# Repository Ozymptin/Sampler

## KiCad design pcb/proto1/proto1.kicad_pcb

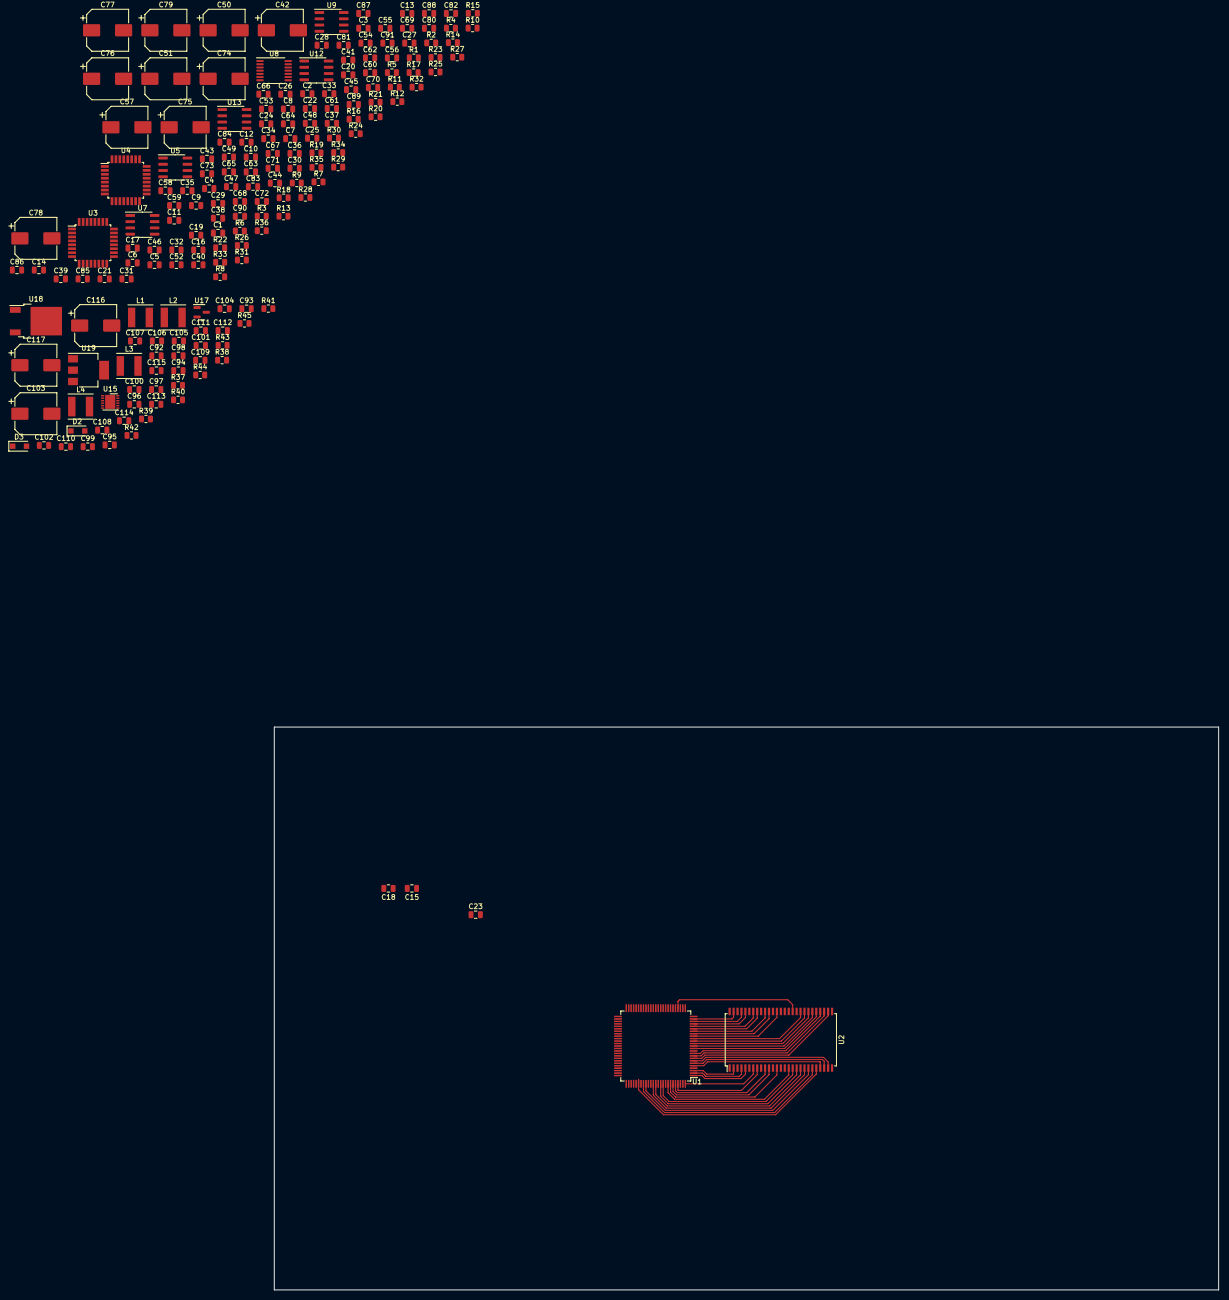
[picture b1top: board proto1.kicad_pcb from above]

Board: 4 copper layers, 191.8 x 114.3 mm, 182 parts (0 on the bottom side), 116 nets.

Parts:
C1, C2, C13, C14, C15, C21, C23, C27, C34, C37, C41, C44, C49, C56, C58, C59, C64, C65, C84, C85, C86, C87, C97, C100, C101, C113, C114, C115: 10uF; C_0805_2012Metric
C3, C4, C5, C6, C16, C17, C18, C19, C20, C22, C24, C25, C26, C28, C29, C30, C32, C33, C35, C36, C39, C40, C43, C46, C47, C48, C53, C54, C55, C60, C61, C66, C67, C88, C89, C90, C91, C92, C94, C98, C99, C102, C108, C109: 0.1uF; C_0805_2012Metric
C7, C8, C38, C45, C110, C111, C112: 1uF; C_0805_2012Metric
C9, C10, C11, C12: C; C_0805_2012Metric
C31, C52, C68, C69, C70, C71, C72, C73, C95, C96: 100pF; C_0805_2012Metric
C42, C50, C51, C57, C74, C75, C76, C77, C78, C79, C103, C116, C117: 220uF; CP_Elec_8x10
C62, C63: 14pF; C_0805_2012Metric
C80, C81, C82, C83: 27pF; C_0805_2012Metric
C93, C104, C105: 1nF; C_0805_2012Metric
C106, C107: 10nF; C_0805_2012Metric
D2, D3: ?; D_SOD-123F
L1, L2: 50uH; L_Taiyo-Yuden_NR-50xx
L3, L4: L; L_Taiyo-Yuden_NR-50xx
R1, R2, R3, R4, R5, R8, R9, R11, R29, R30, R31, R32, R33, R34, R35, R36, R41, R42: 10K; R_0805_2012Metric
R6, R12, R39, R40, R44, R45: 1K; R_0805_2012Metric
R7, R13: 68R; R_0805_2012Metric
R10, R14: 22K; R_0805_2012Metric
R15, R16, R17, R18, R19, R20: 100R; R_0805_2012Metric
R21, R22: 220K; R_0805_2012Metric
R23, R24, R25, R26, R27, R28: 100K; R_0805_2012Metric
R37: 124K; R_0805_2012Metric
R38: 113K; R_0805_2012Metric
R43: 500K; R_0805_2012Metric
U1: ATSAM4C4; LQFP-100_14x14mm_P0.5mm
U2: NDS36P; TSOP-II-54_22.2x10.16mm_P0.8mm
U3, U4: ATSAMD21E17D-A; TQFP-32_7x7mm_P0.8mm
U5, U7, U9, U12, U13: NE5532; SOIC-8_3.9x4.9mm_P1.27mm
U8: PCM1807; TSSOP-14_4.4x5mm_P0.65mm
U15: R1283K; DFN-12-1EP_3x3mm_P0.5mm_EP2.05x2.86mm
U17: ?; SOT-23
U18: ?; TO-252-2
U19: AP7361C-33E; SOT-223-3_TabPin2

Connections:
+1V2: C14.1, C17.1, C22.1, C26.1, C29.1, C36.1, U1.11 (VDDCORE), U1.44 (VDDCORE), U1.53 (VDDPLL), U1.63 (VDDCORE), U1.86 (VDDOUT), U1.89 (VDDCORE)
+3V3: C1.1, C2.1, C3.1, C4.1, C5.1, C6.1, C13.1, C15.1, C16.1, C18.1, C21.1, C23.1, C24.1, C25.1, C28.1, C35.1, C37.1, C39.1, C40.1, C41.1, C43.1, C45.1, C49.1, C53.1, C115.1, U1.33 (VDDIO), U1.34 (VDDBU), U1.49 (VDDIO), U1.76 (VDDIO), U1.85 (VDDIN), U1.92 (VDDLCD), U1.99 (VDDIO), U2.1 (VDD), U2.3 (VDDQ), U2.9 (VDDQ), U2.14 (VDD), U2.27 (VDD), U2.43 (VDDQ), U2.49 (VDDQ), U3.9 (VDDANA), U3.30 (VDDIN), U4.9 (VDDANA), U4.30 (VDDIN), U8.4 (VDD), U19.3 (VO)
+5V: C102.1, C103.1, C110.1, L1.1, U15.8 (Vcc), U15.11 (PVcc), U19.1 (VI)
+5VA: C27.1, C30.1, C34.1, C38.1, U8.3 (VCC)
+12V: C58.1, C60.1, C64.1, C66.1, C84.1, C86.1, C88.1, C90.1, C104.1, C106.1, C108.1, C111.1, C113.1, C116.1, U5.8 (V+), U7.8 (V+), U9.8 (V+), U12.8 (V+), U17.1 (VO)
-12V: C59.2, C61.1, C65.2, C67.1, C85.2, C87.2, C89.1, C91.1, C105.1, C107.1, C109.1, C112.1, C114.1, C117.2, U5.4 (V-), U7.4 (V-), U9.4 (V-), U12.4 (V-), U18.3 (VO)
/A0: U1.81 (PB13/AD3), U2.23 (A0)
/A1: U1.5 (PB19), U2.24 (A1)
/A2: U1.6 (PB8), U2.25 (A2)
/A3: U1.7 (PB22), U2.26 (A3)
/A4: U1.8 (PB30), U2.29 (A4)
/A5: U1.9 (PB25), U2.30 (A5)
/A6: U1.10 (PB24), U2.31 (A6)
/A7: U1.12 (PB29), U2.32 (A7)
/A8: U1.13 (PB9), U2.33 (A8)
/A9: U1.14 (PB10), U2.34 (A9)
/A10: U1.83 (PA4/AD1), U2.22 (A10)
/A11: U1.15 (PB11), U2.35 (A11)
/A12: U1.16 (PB12), U2.36 (A12)
/BA0: U1.87 (PB21), U2.20 (BA0)
/BA1: U1.84 (PA12/AD0), U2.21 (BA1)
/CAS: U1.91 (PB27), U2.17 (~CAS)
/CLK: U1.29 (PC9), U2.38 (CLK)
/CS: U1.88 (PB20), U2.19 (~CS)
/DQ0: U1.3 (PB18), U2.2 (DQ0)
/DQ1: U1.2 (PB7), U2.4 (DQ1)
/DQ2: U1.1 (PB6), U2.5 (DQ2)
/DQ3: U1.100 (PA2), U2.7 (DQ3)
/DQ4: U1.97 (PB17), U2.8 (DQ4)
/DQ5: U1.96 (PA1), U2.10 (DQ5)
/DQ6: U1.95 (PB16), U2.11 (DQ6)
/DQ7: U1.94 (PB28), U2.13 (DQ7)
/DQ8: U1.17 (PB14), U2.42 (DQ8)
/DQ9: U1.18 (PB15), U2.44 (DQ9)
/DQ10: U1.19 (PA26), U2.45 (DQ10)
/DQ11: U1.20 (PA25), U2.47 (DQ11)
/DQ12: U1.21 (PA24), U2.48 (DQ12)
/DQ13: U1.22 (PA20), U2.50 (DQ13)
/DQ14: U1.23 (PA19), U2.51 (DQ14)
/DQ15: U1.24 (PA18), U2.53 (DQ15)
/RAS: U1.90 (PA0), U2.18 (~RAS)
/WE: U1.93 (PB26), U2.16 (~WE)
ADC_CH_CS_0: U1.82 (PA5/AD2), U3.1 (PA00)
ADC_CH_MISO: U1.62 (PA6), U3.8 (PA07)
ADC_CH_MOSI: U1.98 (PA7), U3.7 (PA06)
ADC_CH_SCK: U1.25 (PA8), U3.6 (PA05)
ADC_I2S_FS: U3.14 (PA11), U8.7 (LRCK)
ADC_I2S_MCK: U3.12 (PA09), U8.6 (SCKI)
ADC_I2S_SCK: U3.13 (PA10), U8.8 (BCK)
ADC_I2S_SD: U3.11 (PA08), U8.9 (DOUT)
ADC_LIN: C50.1, U8.13 (VinL)
ADC_RIN: C51.1, U8.14 (VinR)
ADC_SPI_CS: U3.18 (PA17), U8.12 (MS)
ADC_SPI_MOSI: U3.20 (PA19), U8.10 (MD)
ADC_SPI_SCK: U3.19 (PA18), U8.11 (MC)
DAC_CH_CS_0: U1.58 (PC2), U4.1 (PA00)
DAC_CH_MISO: U1.57 (PC3), U4.8 (PA07)
DAC_CH_MOSI: U1.56 (PC4), U4.7 (PA06)
DAC_CH_SCK: U1.55 (PC5), U4.6 (PA05)
EN: R43.1, R45.1, U15.5 (CE)
GND: C1.2, C2.2, C3.2, C4.2, C5.2, C6.2, C7.2, C8.2, C9.1, C10.1, C11.1, C12.1, C13.2, C14.2, C15.2, C16.2, C17.2, C18.2, C19.2, C20.2, C21.2, C22.2, C23.2, C24.2, C25.2, C26.2, C27.2, C28.2, C29.2, C30.2, C32.2, C33.2, C35.2, C36.2, C37.2, C39.2, C40.2, C43.2, C44.2, C46.2, C47.2, C48.2, C49.2, C53.2, C54.2, C55.2, C56.2, C58.2, C59.1, C60.2, C61.2, C62.2, C63.2, C64.2, C65.1, C66.2, C67.2, C68.2, C69.2, C70.1, C71.2, C72.1, C73.2, C82.2, C83.2, C84.2, C85.1, C86.2, C87.1, C88.2, C89.2, C90.2, C91.2, C92.2, C93.2, C94.2, C97.2, C98.2, C99.2, C100.2, C101.2, C102.2, C103.2, C104.2, C105.2, C106.2, C107.2, C108.2, C109.2, C110.2, C111.2, C112.2, C113.2, C114.2, C115.2, C116.2, C117.1, L2.2, R10.2, R14.2, R21.2, R22.2, R23.1, R24.2, R25.1, R26.2, R27.2, R28.2, R33.2, R34.2, R41.1, R43.2, U1.4 (GND), U1.42 (GND), U1.52 (GND), U1.78 (GND), U2.6 (VSSQ), U2.12 (VSSQ), U2.28 (VSS), U2.41 (VSS), U2.46 (VSSQ), U2.52 (VSSQ), U2.54 (VSS), U3.10 (GND), U3.28 (GND), U4.10 (GND), U4.28 (GND), U5.5 (+), U7.3 (+), U8.2 (AGND), U8.5 (DGND), U15.10 (GND), U15.12 (PGND), U15.13 (PAD), U17.3 (GND), U18.1 (GND), U19.2 (GND)
LAUX_OUT: R1.2, U12.1, U12.2 (-)
LOUT: C80.2, R2.2, R35.2, U13.1
unnamed: C7.1, U3.29 (VDDCORE)
unnamed: C8.1, U4.29 (VDDCORE)
unnamed: C9.2, U3.15 (PA14)
unnamed: C10.2, U3.16 (PA15)
unnamed: C11.2, U4.15 (PA14)
unnamed: C12.2, U4.16 (PA15)
unnamed: C31.1, R7.2, U5.1
unnamed: C31.2, R5.2, R6.2, U5.3 (+)
unnamed: C34.2, C38.2, C41.2, C45.2
unnamed: C42.1, R5.1, R6.1, R7.1
unnamed: C42.2, R10.1
unnamed: C44.1, C48.1, U8.1 (VREF)
unnamed: C52.1, R13.2, U9.1
unnamed: C52.2, R11.2, R12.2, U9.3 (+)
unnamed: C57.1, R11.1, R12.1, R13.1
unnamed: C57.2, R14.1
unnamed: C68.1, C74.1, R15.1, R21.1
unnamed: C69.1, C75.1, R16.1, R22.1
unnamed: C70.2, C76.1, R17.1, R23.2
unnamed: C71.1, C77.1, R18.1, R24.1
unnamed: C72.2, C78.1, R19.1, R25.2
unnamed: C73.1, C79.1, R20.1, R26.1
unnamed: C74.2, R27.1, U12.3 (+)
unnamed: C75.2, R28.1, U7.5 (+)
unnamed: C76.2, R29.2
unnamed: C77.2, R30.2
unnamed: C78.2, R31.2
unnamed: C79.2, R32.2
unnamed: C80.1, R29.1, R35.1, U13.2 (-)
unnamed: C81.1, R31.1, R36.1, U9.6 (-)
unnamed: C82.1, R30.1, R33.1, U13.3 (+)
unnamed: C83.1, R32.1, R34.1, U9.5 (+)
unnamed: C92.1, R42.1, U15.7 (Vref)
unnamed: C95.1, R39.2
unnamed: C95.2, R37.2, R41.2, U15.9 (Vfb1)
unnamed: C96.1, R40.2
unnamed: C96.2, R38.2, R42.2, U15.6 (Vfb2)
unnamed: C98.1, C100.1, L3.2, U17.2 (VI)
unnamed: C99.1, C101.1, L4.2, U18.2 (VI)
unnamed: D2.1 (K), L3.1, R37.1, R39.1
unnamed: D2.2 (A), L1.2, U15.2 (Lx1)
unnamed: D3.1 (K), L2.1, U15.3 (Lx2)
unnamed: D3.2 (A), L4.1, R38.1, R40.1, U15.4 (Voutn)
unnamed: R1.1, R2.1, R8.2, U7.2 (-)
unnamed: R3.1, R4.1, R9.2, U5.6 (-)
unnamed: R8.1, U7.1
unnamed: R9.1, U5.7
RAUX_OUT: R3.2, U7.6 (-), U7.7
RESET: U1.48 (NRST), U4.26 (~RESET)
ROUT: C81.2, R4.2, R36.2, U9.7
VBUS: C93.1, C94.1, R44.1
XIN: C62.1, U1.50 (PA30/XIN)
XOUT: C63.1, U1.51 (PA31/XOUT)

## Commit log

2022-02-25 Push
2022-02-25 edited gitignore
2022-02-25 Added kicad files
2022-05-13 Added pcb files
2022-05-13 Eindelijk alles gefixed en ingedeelt
2022-05-13 footprints
2022-05-20 merge
2022-05-23 reworked dram driver
2022-05-25 optimized driver code
2022-05-25 formatting
2022-05-25 more formatting
2022-05-25 driver
